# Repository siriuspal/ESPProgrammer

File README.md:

# ESPProgrammer

A simple ESP32 programmer board over UART protocol.
Can also be used as USB to UART.

Idea is to use a Tag-Connect cable with ESP board instead of adding USB-UART in each board.

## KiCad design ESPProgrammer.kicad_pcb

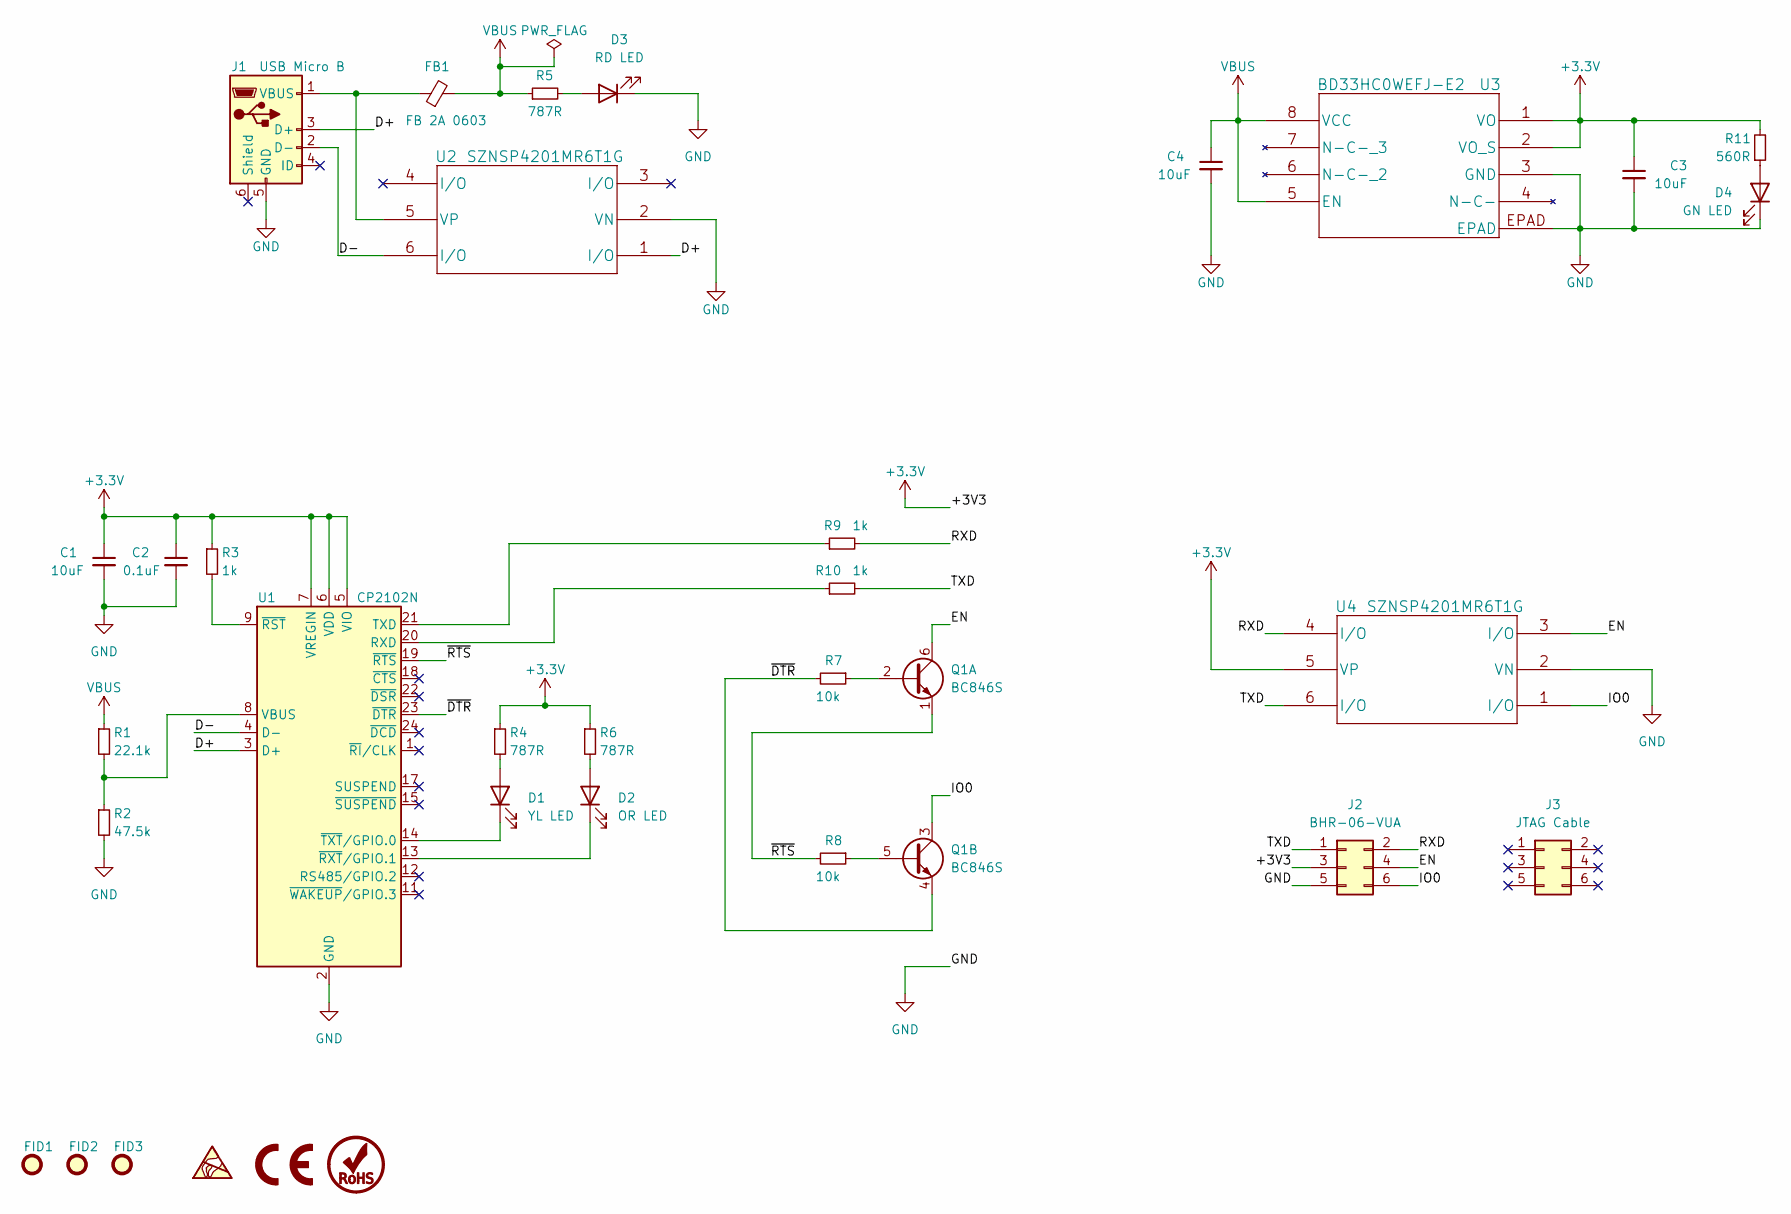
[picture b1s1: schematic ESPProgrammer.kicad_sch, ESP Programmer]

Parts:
C1, C3, C4: 10uF; C_0603_1608Metric; MPN GRM188R61E106KA73J
C2: 0.1uF; C_0603_1608Metric; MPN C0603C104Z3VAC7867
D1: YL LED; LED_0603_1608Metric; MPN SML-311YTT86
D2: OR LED; LED_0603_1608Metric; MPN SML-311DTT86
D3: RD LED; LED_0603_1608Metric; MPN SML-311UTT86
D4: GN LED; LED_0603_1608Metric; MPN SML-310PTT86
FB1: FB 2A 0603; L_0603_1608Metric; MPN MPZ1608S181ATAH0
FID1, FID2, FID3: Fiducial; Fiducial_0.5mm_Mask1mm
J1: USB Micro B; USB_Micro-B_Amphenol_10118194_Horizontal; MPN 10118194-0001LF
J2: BHR-06-VUA; PinHeader_2x03_P2.54mm_Vertical; MPN BHR-06-VUA
J3: JTAG Cable; MPN TC2030-IDC-NL
Q1: BC846S; SOT-363_SC-70-6; MPN BC846S,125
R1: 22.1k; R_0603_1608Metric; MPN RC0603FR-1322K1L
R2: 47.5k; R_0603_1608Metric; MPN RC0603FR-0747K5L
R3, R9, R10: 1k; R_0603_1608Metric; MPN AC0603JR-071KL
R4, R5, R6: 787R; R_0603_1608Metric; MPN RC0603FR-07787RL
R7, R8: 10k; R_0603_1608Metric; MPN RT0603FRE0710KL
R11: 560R; R_0603_1608Metric; MPN RC0603JR-07560RL
U1: CP2102N; QFN-24-1EP_4x4mm_P0.5mm_EP2.6x2.6mm; MPN CP2102N-A02-GQFN24R
U2, U4: SZNSP4201MR6T1G; TSOP-6_1.65x3.05mm_P0.95mm; MPN SZNSP4201MR6T1G
U3: BD33HC0WEFJ-E2; HTSOP-8-1EP_3.9x4.9mm_P1.27mm_EP2.4x3.2mm; MPN BD33HC0WEFJ-E2

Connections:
+3V3: C1.1, C2.1, C3.1, J2.3, R3.1, R4.1, R6.1, R11.2, U1.5 (VIO), U1.6 (VDD), U1.7 (VREGIN), U3.1 (VO), U3.2 (VO_S), U4.5 (VP)
/D+: J1.3 (D+), U1.3 (D+), U2.1 (I/O)
/D-: J1.2 (D-), U1.4 (D-), U2.6 (I/O)
/EN: J2.4, Q1.6 (C1), U4.3 (I/O)
/IO0: J2.6, Q1.3 (C2), U4.1 (I/O)
/RXD: J2.2, R9.2, U4.4 (I/O)
/TXD: J2.1, R10.2, U4.6 (I/O)
/~DTR: Q1.4 (E2), R7.2, U1.23 (~DTR)
/~RTS: Q1.1 (E1), R8.2, U1.19 (~RTS)
GND: C1.2, C2.2, C3.2, C4.2, D3.1 (K), D4.1 (K), J1.5 (GND), J2.5, R2.2, U1.2 (GND), U1.25 (GND), U2.2 (VN), U3.3 (GND), U3.EPAD, U4.2 (VN)
unnamed: D1.1 (K), U1.14 (~TXT/GPIO.0)
unnamed: D1.2 (A), R4.2
unnamed: D2.1 (K), U1.13 (~RXT/GPIO.1)
unnamed: D2.2 (A), R6.2
unnamed: D3.2 (A), R5.2
unnamed: D4.2 (A), R11.1
unnamed: FB1.1, J1.1 (VBUS), U2.5 (VP)
unnamed: Q1.2 (B1), R7.1
unnamed: Q1.5 (B2), R8.1
unnamed: R1.2, R2.1, U1.8 (VBUS)
unnamed: R3.2, U1.9 (~RST)
unnamed: R9.1, U1.21 (TXD)
unnamed: R10.1, U1.20 (RXD)
VBUS: C4.1, FB1.2, R1.1, R5.1, U3.5 (EN), U3.8 (VCC)

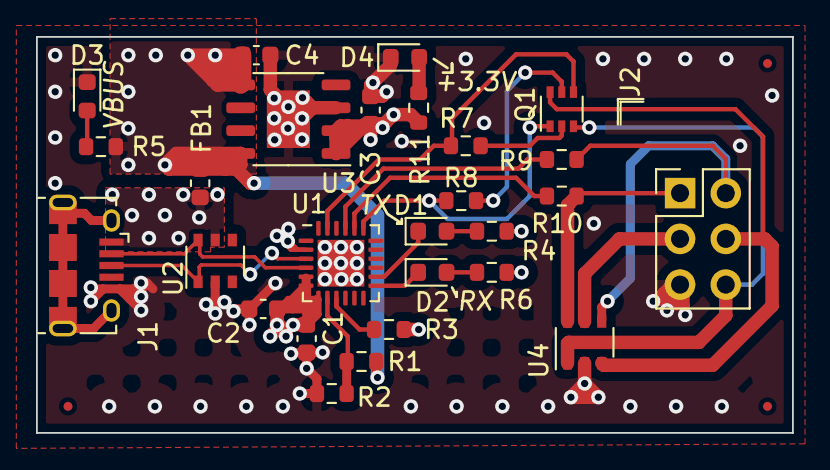
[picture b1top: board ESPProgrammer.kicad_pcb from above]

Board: 4 copper layers, 42.0 x 22.0 mm, 30 parts (0 on the bottom side), 24 nets.

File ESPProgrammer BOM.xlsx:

Item | Qty | Reference(s) | Value | MPN | Manufacturer | Substitute Allowed | Description | LibPart | Footprint | Datasheet
1 | 3 | C1, C3, C4 | 10uF | GRM188R61E106KA73J | Murata Electronics | Yes | CAP CER 10UF 25V X5R 0603 | Device:C_Small | Capacitor_SMD:C_0603_1608Metric | ~
2 | 1 | C2 | 0.1uF | C0603C104Z3VAC7867 | KEMET | Yes | CAP CER 0.1UF 25V Y5V 0603 | Device:C_Small | Capacitor_SMD:C_0603_1608Metric | ~
3 | 1 | D1 | YL LED | SML-311YTT86 | Rohm Semiconductor | Yes | LED YELLOW CLEAR 0603 SMD | Device:LED | LED_SMD:LED_0603_1608Metric | ~
4 | 1 | D2 | OR LED | SML-311DTT86 | Rohm Semiconductor | Yes | LED ORANGE CLEAR 0603 SMD | Device:LED | LED_SMD:LED_0603_1608Metric | ~
5 | 1 | D3 | RD LED | SML-311UTT86 | Rohm Semiconductor | Yes | LED RED CLEAR 0603 SMD | Device:LED | LED_SMD:LED_0603_1608Metric | ~
6 | 1 | D4 | GN LED | SML-310PTT86 | Rohm Semiconductor | Yes | LED GREEN CLEAR 0603 SMD | Device:LED | LED_SMD:LED_0603_1608Metric | ~
7 | 1 | FB1 | FB 2A 0603 | MPZ1608S181ATAH0 | TDK Corporation | Yes | FERRITE BEAD 180 OHM 0603 1LN 2A | Device:FerriteBead_Small | Inductor_SMD:L_0603_1608Metric | ~
8 | 1 | J1 | USB Micro B | 10118194-0001LF | Amphenol ICC (FCI) | Yes | CONN RCPT USB2.0 MICRO B SMD R/A with TH Support Pins | Connector:USB_B_Micro | Connector_USB:USB_Micro-B_Amphenol_10118194_Horizontal | ~
9 | 1 | J2 | BHR-06-VUA | BHR-06-VUA | Adam Tech | Yes | CONN HEADER VERT 6POS 2.54MM | Connector_Generic:Conn_02x03_Odd_Even | Connector_PinSocket_2.54mm:PinSocket_2x03_P2.54mm_Vertical | ~
10 | 1 | J3 | JTAG Cable | TC2030-IDC-NL | Tag-Connect | No | â€œNo Legsâ€ 6-pin Plug-of-Nailsâ„¢ Cable fitted with a 6-pin 0.1â€³ pitch rib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 | Connector_Generic:Conn_02x03_Odd_Even |  | https://www.tag-connect.com/product/tc2030-idc-nl
11 | 1 | Q1 | BC846S | BC846S,125 | Nexperia USA Inc. | Yes | TRANS 2NPN 65V 0.1A 6TSSOP | Device:Q_Dual_NPN_NPN_E1B1C2E2B2C1 | Package_TO_SOT_SMD:SOT-363_SC-70-6 | ~
12 | 1 | R1 | 22.1k | RC0603FR-1322K1L | YAGEO | Yes | RES 22.1K OHM 1% 1/10W 0603 | Device:R_Small | Resistor_SMD:R_0603_1608Metric | ~
13 | 1 | R2 | 47.5k | RC0603FR-0747K5L | YAGEO | Yes | RES 47.5K OHM 1% 1/10W 0603 | Device:R_Small | Resistor_SMD:R_0603_1608Metric | ~
14 | 3 | R3, R9, R10 | 1k | AC0603JR-071KL | YAGEO | Yes | RES SMD 1K OHM 5% 1/10W 0603 | Device:R_Small | Resistor_SMD:R_0603_1608Metric | ~
15 | 3 | R4, R5, R6 | 787R | RC0603FR-07787RL | YAGEO | Yes | RES 787 OHM 1% 1/10W 0603 | Device:R_Small | Resistor_SMD:R_0603_1608Metric | ~
16 | 2 | R7, R8 | 10k | RT0603FRE0710KL | YAGEO | Yes | RES SMD 10K OHM 1% 1/10W 0603 | Device:R_Small | Resistor_SMD:R_0603_1608Metric | ~
17 | 1 | R11 | 560R | RC0603JR-07560RL | YAGEO | Yes | RES 560 OHM 5% 1/10W 0603 | Device:R_Small | Resistor_SMD:R_0603_1608Metric | ~
18 | 1 | U1 | CP2102N | CP2102N-A02-GQFN24R | Silicon Labs | No | IC USB TO UART BRIDGE QFN24 | Interface_USB:CP2102N-Axx-xQFN24 | Package_DFN_QFN:QFN-24-1EP_4x4mm_P0.5mm_EP2.6x2.6mm | https://www.silabs.com/documents/public/data-sheets/cp2102n-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
19 | 2 | U2, U4 | SZNSP4201MR6T1G | SZNSP4201MR6T1G | onsemi | Yes | TVS DIODE 5VWM 12VC 6TSOP | Diode:SZNSP4201MR6T1G | Package_SO:TSOP-6_1.65x3.05mm_P0.95mm
20 | 1 | U3 | BD33HC0WEFJ-E2 | BD33HC0WEFJ-E2 | Rohm Semiconductor | No | IC REG LINEAR 3.3V 1A 8HTSOP | Power_Management:BD33HC0WEFJ-E2 | Package_SO:HTSOP-8-1EP_3.9x4.9mm_P1.27mm_EP2.4x3.2mm

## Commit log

2021-12-27 Create LICENSE
2021-12-28 Completed the design
